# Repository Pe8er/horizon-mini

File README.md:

# Horizon *Mini* Keyboard

### Note:

This is a mod of the original, gorgeous Horizon. Changelog:

- Removed 2 columns
- Fully wireless: added battery connector & power switch
- Replaced Horizon logos with Tool (band) heptagram graphics

# [⬇️ Download latest Gerbers](https://github.com/Pe8er/horizon-mini/releases/latest)

### Original readme below 👇

# Horizon Keyboard

Horizon is a 44 key (4x12) ortholinear keyboard, powered by an Arduino Pro Micro.

This keyboard is a grid of 1U keys with no special features: no hotswap, no RGB, no OLED screen, no knobs.

## Project structure

* [`gerbers`](gerbers): Gerber files for PCB manufacturing
* [`graphics`](graphics): Source assets for PCB silkscreen
* [`kicad`](kicad): KiCad project files (schematics and PCB designs)
* [`kicad-libraries`](kicad-libraries): KiCad components and footprints
* [`kicad-plugins`](kicad-plugins): KiCad Pcbnew Python plugins
* [`images`](images): Images for project documentation

## PCBs

Two separate PCB designs are available for MX and Choc keyswitches, with their respective footprints and key spacing (MX: 19mm x 19mm, Choc: 18mm x 17mm).

Each design consists of a main PCB, a top plate to protect the microcontroller, and a bottom plate to protect the bottom components:

The bottom plate is a cutout of all the components exposed through the bottom of the main PCB, and screws *directly* against the main PCB. This nicely guards you and your desk surface from all the pointy through-hole bits, while retaining a low keyboard height:

## KiCad project notes

The bottom and top plates are generated via a custom KiCad 7 Python SWIG plugin [Horizon Board Producer](kicad-plugins/horizon-board-producer-plugin.py).

For the plugin to generate these plate boards, the PCB and its footprints use the following layer convention:

* `F.Adhesive` designates top plate holes and edge cuts.
* `B.Adhesive` designates bottom plate holes and edge cuts.

When the board producer runs, these layers are used as follows:

* On the board and footprints:
    * Graphics on the plate's designated layer will be moved to `Edge.Cuts` when producing that plate.
    * As with all edge cuts, please make sure your graphics are non-overlapping closed shapes.
* On footprints only:
    * Pads of type "SMD Aperture" and shape "Circular/Oval" on the plate's designated layer will be converted to proper NPTH pads.
    * Note only circular/oval shapes are supported for these pads, because they are the only available hole/drill shapes. If you need a fancy plate cutout shape on your footprint, then draw graphics lines on the designated layer.
    * **IMPORTANT**: When adding pads solely for plate cutout purposes, set the technical layer to just the designated plate cutout layers. Leave all other technical layers unchecked.

Additionally, the board producer plugin will preserve any in-bounds "H" footprint pads (mounting holes), "LOGO" footprint graphics (custom silkscreen art), and board silkscreen on the plates. Other items which are not needed for plates (e.g., copper tracks and zones) are removed from the plates.

The board producer plugin also generates all the Gerber files for production.

Please note the board producer plugin expects the following folder structure:

* The KiCad PCB file is two folders deep from the project root, e.g., `kicad/[board-version]/[board-name].kicad_pcb`
* When the plugin executes, a folder called `temp` is created in the project root to store any temporary files created.
    * Each time the board producer runs, any existing files in this temporary folder are deleted.

**IMPORTANT:** If you would like to use this plugin and plate edge cuts convention for you own project, please make sure you carefully examine the output Gerber files! The plugin ultimately worked well for my case, but you might need to make adjustments to the plugin to suit your project. And to reduce the chance of being charged extra money by PCB manufacturers, use footprint plate holes instead of edge cuts whenever reasonable to do so.

**IMPORTANT:** This plugin uses `pcbnew.LoadBoard()` to load copies of the PCB, which is [not safely supported in a running instance of KiCad](https://forum.kicad.info/t/the-loadboard-function-is-invalid/31238/9). To avoid project integrity problems this may cause to the running KiCad instance, the plugin forcefully exits KiCad upon execution completion.

## Keyboard firmware

* ZMK only. Horizon Mini's shield definition is in [Pe8er's zmk-config](https://github.com/Pe8er/zmk-config-horizon-mini).

## Bill of materials

For PCBs, keyswitches, and keycaps, get parts depending on your desired keyswitch type.

Part | Purpose | Quantity | Notes | Vendor URL
---- | ------- | -------- | --------- | ----------
Main PCB  | circuit board | 1 | | Send Gerber zip files to [JLCPCB](https://jlcpcb.com/).
Top plate PCB  | protects microcontroller | 1 | 
Bottom plate PCB  | protects bottom pins and components | 1 |
Arduino Pro Micro | Microcontroller board | 1 | Or use another Pro Micro compatible board with same dimensions (confirmed Elite-C V4, nice!nano 2.0, and Adafruit KB2040 fit) | [AliExpress (TENSTAR ROBOT) - Micro USB 3-18V](https://www.aliexpress.com/item/32849563958.html)
Sockets | so you don't need to solder the MCU itself | 1 | | [Aliexpress](https://www.aliexpress.com/item/1777652709.html?spm=a2g0o.order_list.order_list_main.29.55371802cNThgI)
MSK-12C02 | Power switch | 1 | | [Aliexpress](https://www.aliexpress.com/item/4000685483225.html?spm=a2g0o.order_list.order_list_main.11.55371802cNThgI)
6x6mm DIP 4-pin tactile switch | Reset button | 1 | | [AliExpress (xin cheng electronic)- 6x6x10mm](https://www.aliexpress.com/item/32912263133.html)
1N4148 SOD-123 | Diodes for keyboard row-column matrix | 52 | | [AliExpress (DSSRQI) - 1N4148 SOD-123](https://www.aliexpress.com/item/4000331408283.html)
Battery | to eliminate wires | 1
Battery socket | to plug into the PCB | 1
Keyswitches |  | 44 | PCB mount (5 pin) switches recommended | MX: [AliExpress (KPrepublic) - Gateron Switch RGB 5pin Clear](https://www.aliexpress.com/item/3256801798608641.html), Choc: [MKUltra Corporation - Kailh Low Profile Choc Switches](https://mkultra.click/choc-switches)
Keycaps |  | 44 | | MX: [AliExpress (Cool Jazz)- DSA 1U Keycaps](https://www.aliexpress.com/item/2251832643863132.html), Choc: [MKUltra Corporation - MBK Choc Keycaps](https://mkultra.click/mbk-choc-keycaps) / [wrk. Legend](https://worklouder.cc/shop/wrk-legend/)
M2 6mm screws | Secure main PCB and plate PCBs | 8 | | [AliExpress (wuhushiyu) - 200PCS-M2 Mix - Black](https://www.aliexpress.com/item/32862529967.html)
M2 nuts | Secure main PCB and plate PCBs | 8 | | See M2 set above
M2 8mm male-female standoffs | Raise top plate PCB above microcontroller | 4 | | See M2 set above
2mm tall rubber bumpons | Raise board above desk surface and provide skid resitance | 6 | Shop around - you can get cheaper alternatives if you don't need 96 of them! | [Amazon - 3M SJ5302 Clear Bumpon Blister Pack (96 Bumpons)](https://www.amazon.com/SJ5302-Clear-Bumpon-Blister-Bumpons/dp/B01ACPT2LU) / [Aliexpress](https://www.aliexpress.com/item/32962113640.html?spm=a2g0o.order_list.order_list_main.5.55371802cNThgI) / [Aliexpress](https://www.aliexpress.com/item/1005005615951861.html?spm=a2g0o.order_list.order_list_main.17.55371802cNThgI)

M2 standoff height requirements are dependent on the seated microcontroller height. An M2 spacer set should give you enough options. I recommend getting a reset button ~2mm taller than the M2 standoffs so the button is level with the top plate.

If using a LiPo battery and a bluetooth Pro Micro compatible board, then use battery size 301230. Just make sure the microcontroller socket height provides clearance for the battery to fit underneath (standard SIP sockets are a common choice).

## PCB manufacturing settings

These are the manufacturing settings I used when ordering from JLCPCB:

* **Base Material**: FR4
* **Layers**: 2
* **Dimensions**: (whatever the gerber file specifies)
* **PCB Qty**: 5
* **Different Design**: 1
* **Delivery Format**: Single PCB
* **PCB Thickness**: 1.6
* **PCB Color**: Black
* **Silkscreen**: White
* **Surface Finish**: LeadFree HASL-RoHS
* **Outer Copper Weight**: 1 oz
* **Gold Fingers**: No
* **Confirm Production File**: No
* **Flying Probe Test**: Fully Test
* **Castellated Holes**: No
* **Remove Order Number**: Specify a location

**IMPORTANT:** All PCBs have ["JLCJLCJLCJLC" silkscreen text](https://support.jlcpcb.com/article/28-how-to-remove-order-number-from-your-pcb) underneath the Pro Micro footprint. If you want to remove the order number from the boards or you want to print the PCBs with another manufacturer, then I recommend removing this silkscreen text from the `.kicad_pcb` file, and then re-run the Horizon Board Producer plugin to create the updated Gerber files.

## Build tips

* The main PCB uses a ground plane, so ground pads are more stubborn to solder. Make sure your soldering tip has good surface area coverage across the pad and component leg. If your soldering iron supports it, turning up the temperature a bit can help too.
* Before soldering the keyswitches, make sure they are perfectly straight and fully inserted into the PCB. Put the keycaps on the inserted keyswitches, and give a thorough visual inspection for any spacing or height irregularities between the keycaps. For MX builds, Gateron switches in particular have thicker PCB-mount pins - push these keyswitches in hard to make sure they are fully inserted!
* To get a perfect fit between the main PCB and bottom plate, keep your soldering tidy! Clean any excess solder/flux which falls outside the bounds of the bottom plate cutouts.
* Attaching the main PCB and the bottom plate requires a very steady hand. The approach that worked best for me was using narrow tweezers to grip the edges of the hex nut against the main PCB, while driving in the screw from the bottom plate.
* The top plate is a very tight fit. If the inner keycaps rub against it, first ensure the top plate is perfectly centered. To center it, slide a thin piece of cardstock in-and-out between the inner keycaps and the top plate on all sides. If that does not resolve the keycaps rubbing, then remove the top plate, sand its edges a bit, and try again.

## Revision history

* **Rev1** (2021-07-30 - not publicly released):
    * PCB: Experimental prototype of MX board.
    * Schematic: Wire as 42 key 7x6 matrix (original release only had 6 keys on bottom row).
* **Rev2** (2021-09-26)
    * PCB: Create MX and Choc boards with bottom and top plates.
    * Schematic: Wire as 52 key 4x14 matrix.
* **Rev2.1** (2021-10-24)
    * PCB: Slightly improve thermal relief clearance to make soldering ground pads easier.
* **Rev2.2** (2021-10-25)
    * Horizon Board Producer plugin: Now supports converting designated placeholder pads to NPTH pads during plate generation.
    * Footprints: Replace graphics which indicate plate cutouts with placeholder pads which indicate plate NPTH pads.
    * PCB: Gerber files regenerated using updated board producer plugin.
* **Rev2.3** (2022-03-21)
    * Horizon Board Producer plugin: Upgrade to KiCad 6
    * PCB, Schematic: No physical changes. Files upgraded to KiCad 6, and Gerber files regenerated using updated files.
* **Rev2.4** (2023-11-09)
    * Horizon Board Producer plugin: Upgrade to KiCad 7
    * PCB, Schematic: No physical changes. Files upgraded to KiCad 7, and Gerber files regenerated using updated files.

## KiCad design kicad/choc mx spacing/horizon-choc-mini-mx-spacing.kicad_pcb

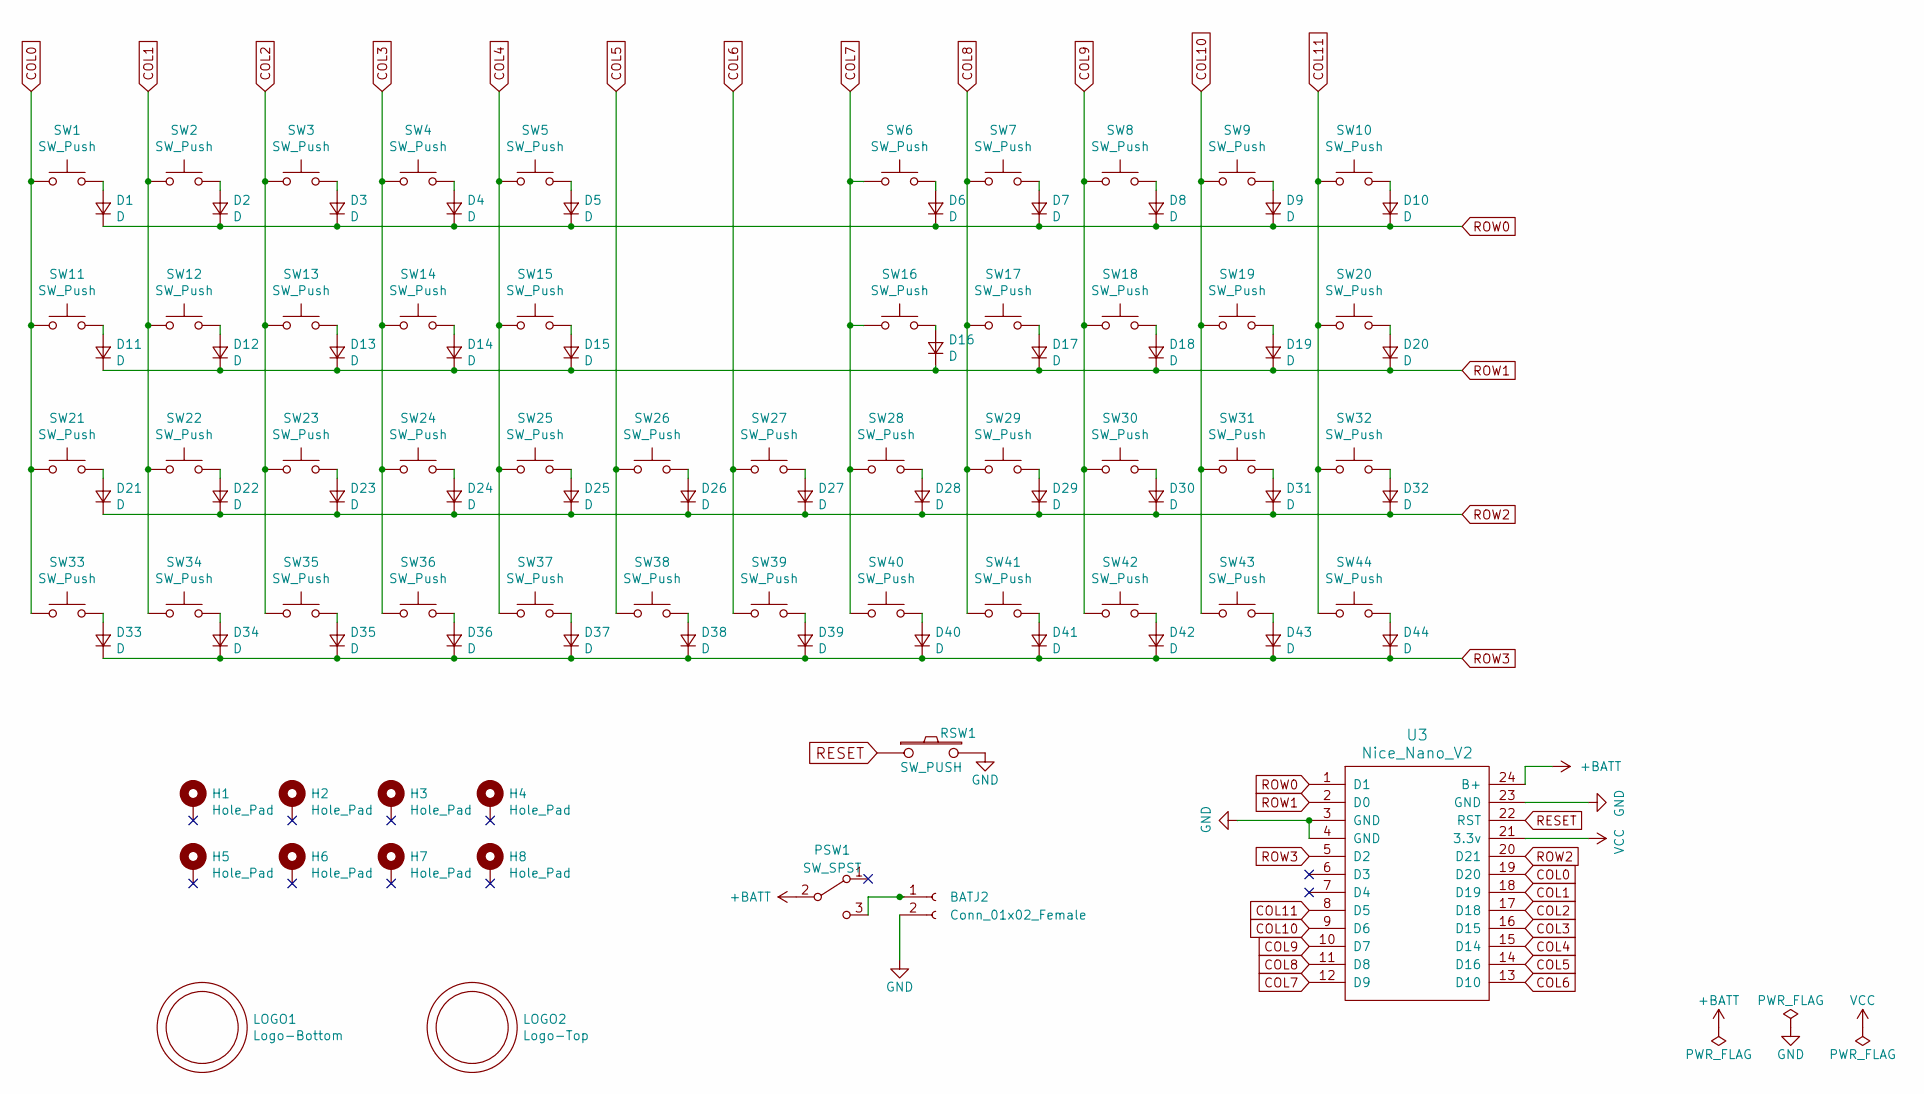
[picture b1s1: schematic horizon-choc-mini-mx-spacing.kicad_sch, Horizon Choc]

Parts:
BATJ2: Conn_01x02_Female; JST_PH_S2B-PH-K_1x02_P2.00mm_Horizontal
D1, D2, D3, D4, D5, D6, D7, D8, D9, D10, D11, D12, D13, D14, D15, D16, D17, D18, D19, D20, D21, D22, D23, D24, D25, D26, D27, D28, D29, D30, D31, D32, D33, D34, D35, D36, D37, D38, D39, D40, D41, D42, D43, D44: D; D_SOD-123
H1, H2, H3, H4, H5, H6, H7, H8: Hole_Pad; Mount_M2
LOGO1: Logo-Bottom; bloodborne_moon
LOGO2: Logo-Top; bloodborne_moon
PSW1: SW_SPST; SW_SPDT_PCM12
RSW1: SW_PUSH; SW_Push_6mm
SW1, SW2, SW3, SW4, SW5, SW6, SW7, SW8, SW9, SW10, SW11, SW12, SW13, SW14, SW15, SW16, SW17, SW18, SW19, SW20, SW21, SW22, SW23, SW24, SW25, SW26, SW27, SW28, SW29, SW30, SW31, SW32, SW33, SW34, SW35, SW36, SW37, SW38, SW39, SW40, SW41, SW42, SW43, SW44: SW_Push; SW_Choc_MX
U3: Nice_Nano_V2; Nice_Nano_V2_Flipped

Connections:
+BATT: PSW1.2 (B), U3.24 (B+)
COL0: SW1.1, SW11.1, SW21.1, SW33.1, U3.19 (D20)
COL1: SW2.1, SW12.1, SW22.1, SW34.1, U3.18 (D19)
COL2: SW3.1, SW13.1, SW23.1, SW35.1, U3.17 (D18)
COL3: SW4.1, SW14.1, SW24.1, SW36.1, U3.16 (D15)
COL4: SW5.1, SW15.1, SW25.1, SW37.1, U3.15 (D14)
COL5: SW26.1, SW38.1, U3.14 (D16)
COL6: SW27.1, SW39.1, U3.13 (D10)
COL7: SW6.1, SW16.1, SW28.1, SW40.1, U3.12 (D9)
COL8: SW7.1, SW17.1, SW29.1, SW41.1, U3.11 (D8)
COL9: SW8.1, SW18.1, SW30.1, SW42.1, U3.10 (D7)
COL10: SW9.1, SW19.1, SW31.1, SW43.1, U3.9 (D6)
COL11: SW10.1, SW20.1, SW32.1, SW44.1, U3.8 (D5)
GND: BATJ2.2, U3.3 (GND), U3.4 (GND), U3.23 (GND); also elsewhere on the board
unnamed: BATJ2.1, PSW1.3 (C)
unnamed: D1.2 (A), SW1.2
unnamed: D2.2 (A), SW2.2
unnamed: D3.2 (A), SW3.2
unnamed: D4.2 (A), SW4.2
unnamed: D5.2 (A), SW5.2
unnamed: D6.2 (A), SW6.2
unnamed: D7.2 (A), SW7.2
unnamed: D8.2 (A), SW8.2
unnamed: D9.2 (A), SW9.2
unnamed: D10.2 (A), SW10.2
unnamed: D11.2 (A), SW11.2
unnamed: D12.2 (A), SW12.2
unnamed: D13.2 (A), SW13.2
unnamed: D14.2 (A), SW14.2
unnamed: D15.2 (A), SW15.2
unnamed: D16.2 (A), SW16.2
unnamed: D17.2 (A), SW17.2
unnamed: D18.2 (A), SW18.2
unnamed: D19.2 (A), SW19.2
unnamed: D20.2 (A), SW20.2
unnamed: D21.2 (A), SW21.2
unnamed: D22.2 (A), SW22.2
unnamed: D23.2 (A), SW23.2
unnamed: D24.2 (A), SW24.2
unnamed: D25.2 (A), SW25.2
unnamed: D26.2 (A), SW26.2
unnamed: D27.2 (A), SW27.2
unnamed: D28.2 (A), SW28.2
unnamed: D29.2 (A), SW29.2
unnamed: D30.2 (A), SW30.2
unnamed: D31.2 (A), SW31.2
unnamed: D32.2 (A), SW32.2
unnamed: D33.2 (A), SW33.2
unnamed: D34.2 (A), SW34.2
unnamed: D35.2 (A), SW35.2
unnamed: D36.2 (A), SW36.2
unnamed: D37.2 (A), SW37.2
unnamed: D38.2 (A), SW38.2
unnamed: D39.2 (A), SW39.2
unnamed: D40.2 (A), SW40.2
unnamed: D41.2 (A), SW41.2
unnamed: D42.2 (A), SW42.2
unnamed: D43.2 (A), SW43.2
unnamed: D44.2 (A), SW44.2
RESET: U3.22 (RST); also elsewhere on the board
ROW0: D1.1 (K), D2.1 (K), D3.1 (K), D4.1 (K), D5.1 (K), D6.1 (K), D7.1 (K), D8.1 (K), D9.1 (K), D10.1 (K), U3.1 (D1)
ROW1: D11.1 (K), D12.1 (K), D13.1 (K), D14.1 (K), D15.1 (K), D16.1 (K), D17.1 (K), D18.1 (K), D19.1 (K), D20.1 (K), U3.2 (D0)
ROW2: D21.1 (K), D22.1 (K), D23.1 (K), D24.1 (K), D25.1 (K), D26.1 (K), D27.1 (K), D28.1 (K), D29.1 (K), D30.1 (K), D31.1 (K), D32.1 (K), U3.20 (D21)
ROW3: D33.1 (K), D34.1 (K), D35.1 (K), D36.1 (K), D37.1 (K), D38.1 (K), D39.1 (K), D40.1 (K), D41.1 (K), D42.1 (K), D43.1 (K), D44.1 (K), U3.5 (D2)
VCC: U3.21 (3.3v)

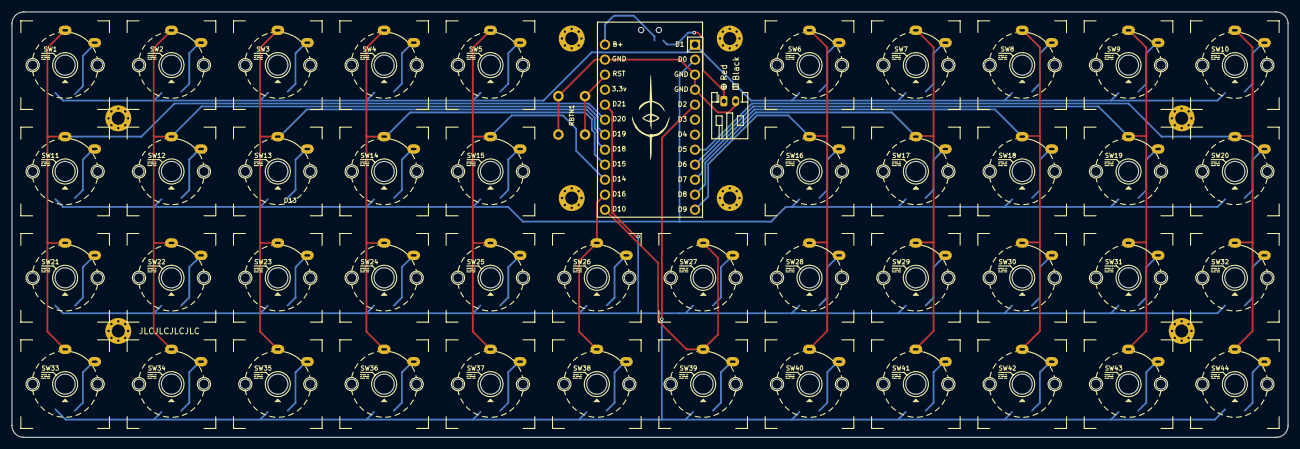
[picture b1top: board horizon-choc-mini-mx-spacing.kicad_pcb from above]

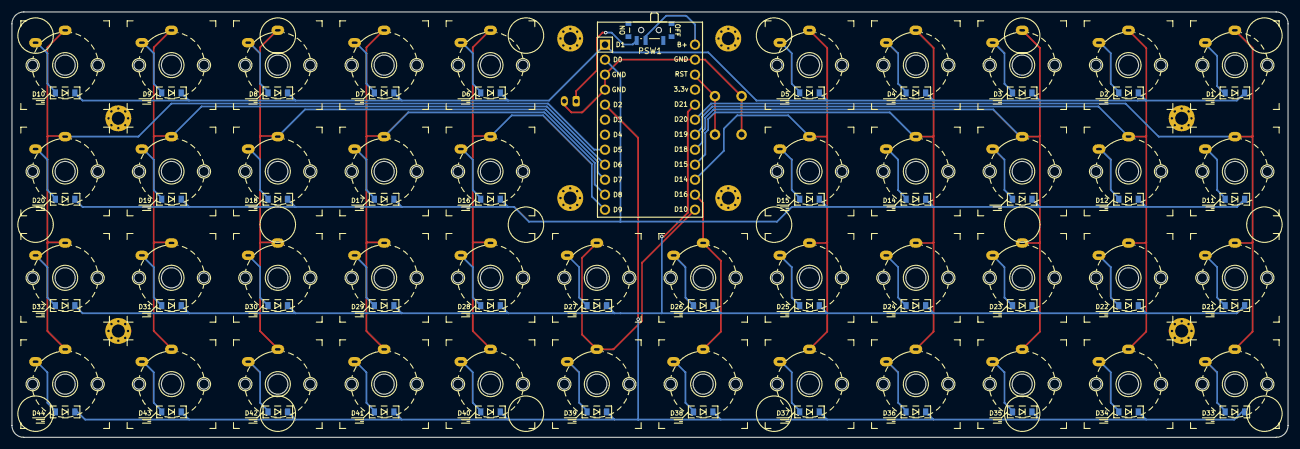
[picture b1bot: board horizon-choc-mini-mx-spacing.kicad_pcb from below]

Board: 2 copper layers, 216.0 x 72.0 mm, 102 parts (45 on the bottom side), 64 nets.

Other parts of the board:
RBTN1: SW_PUSH; SW_Push_6mm

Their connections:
GND: RBTN1.2; also elsewhere on the board
RESET: RBTN1.1; also elsewhere on the board

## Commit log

2023-08-31 First upload
2023-08-31 Add .DS_Store to ignored files
2023-11-09 Almost there
2023-11-14 Submitting to JLCPCB!
2023-11-14 Update progress in Readme
2023-11-14 Update Readme to match the latest updates
2023-12-18 - Updated and cleaned wiring - Added bottom plate holes for battery connector - New graphics (Tool heptagram) - Added teardrops - Added rubber feet markings - Made footprints more descriptive: diodes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
2023-12-18 Add board renders
2023-12-18 Added heptagram render
2023-12-18 Include download link in readme
2024-01-23 - Fix flipped MCU footprint - Fix power switch label
2024-01-23 Fixes #3; Update readme with image
